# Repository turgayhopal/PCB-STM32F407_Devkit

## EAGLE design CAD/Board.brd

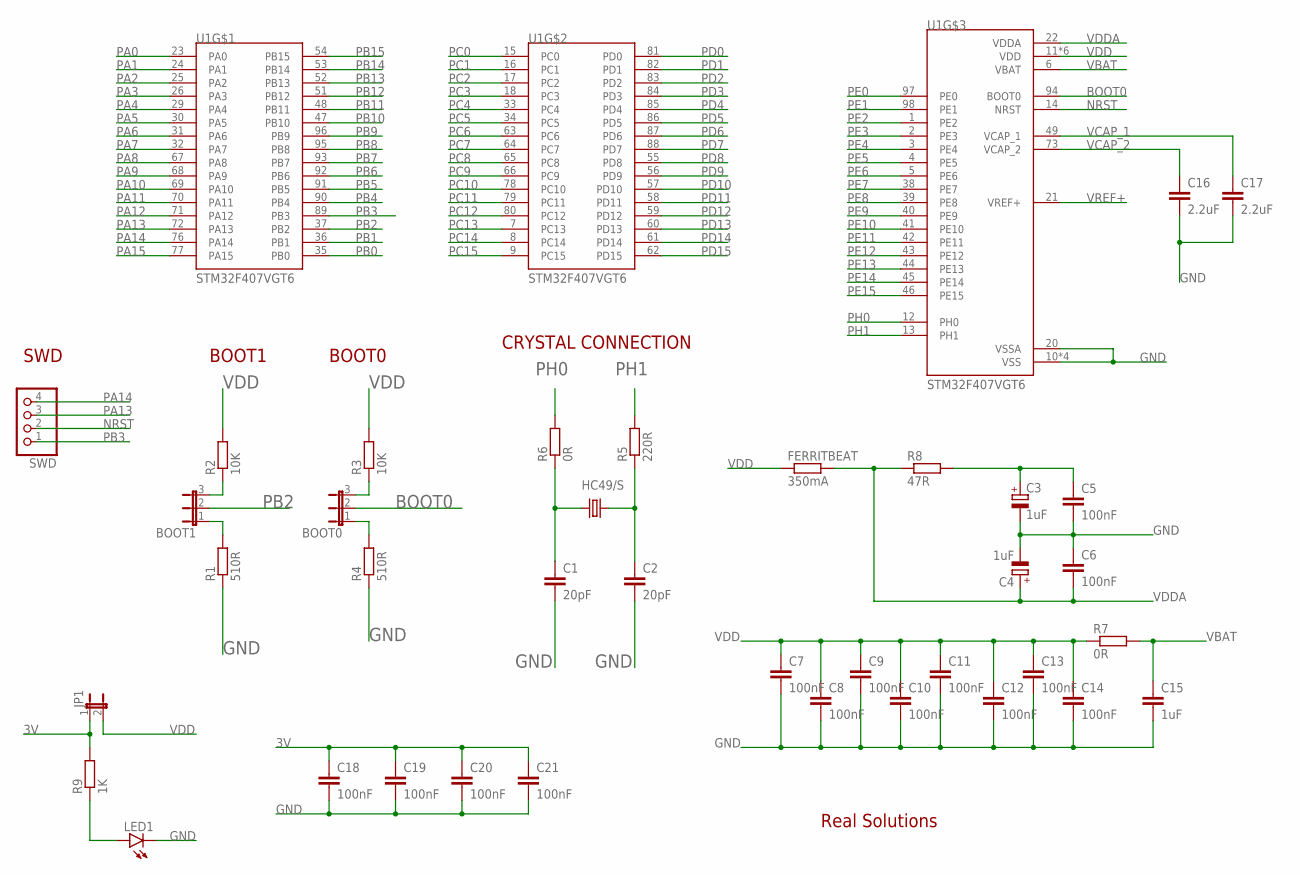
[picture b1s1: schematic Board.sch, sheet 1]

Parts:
BOOT0, BOOT1: JP2E; JP2
C1, C2: 20pF; C0805
C3, C4: 1uF; SMC_A
C5, C6, C7, C8, C9, C10, C11, C12, C13, C14, C18, C19, C20, C21: 100nF; C0805
C15: 1uF; C0805
C16, C17: 2.2uF; C0805
FERRITBEAT: 350mA; R1206
HC49/S: CRYSTALHC49S; HC49/S
JP1: JP1E; JP1
LED1: LEDCHIP-LED0805; CHIP-LED0805
R1, R4: 510R; R0805
R2, R3: 10K; R0805
R5: 220R; R0805
R6, R7: 0R; R0805
R8: 47R; R0805
R9: 1K; R0805
SWD: PINHD-1X4; 1X04
U1: STM32F407VGT6; QFP50P1600X1600X160-100N

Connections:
3V: C18.1, C19.1, C20.1, C21.1, JP1.1, R9.2; also elsewhere on the board
BOOT0: BOOT0.2, U1.94 (BOOT0)
GND: C1.2, C2.2, C3.-, C4.-, C5.2, C6.1, C7.2, C8.2, C9.2, C10.2, C11.2, C12.2, C13.2, C14.2, C15.2, C16.2, C17.2, C18.2, C19.2, C20.2, C21.2, LED1.C, R1.1, R4.1, U1.10 (VSS), U1.20 (VSSA), U1.27 (VSS), U1.74 (VSS), U1.99 (VSS); also elsewhere on the board
unnamed: C1.1, HC49/S.1, R6.1
unnamed: C2.1, HC49/S.2, R5.1
unnamed: BOOT1.3, R2.1
unnamed: BOOT1.1, R1.2
unnamed: BOOT0.3, R3.1
unnamed: BOOT0.1, R4.2
unnamed: LED1.A, R9.1
unnamed: C3.+, C5.1, R8.2
NRST: SWD.2, U1.14 (NRST); also elsewhere on the board
PA0: U1.23 (PA0); also elsewhere on the board
PA1: U1.24 (PA1); also elsewhere on the board
PA2: U1.25 (PA2); also elsewhere on the board
PA3: U1.26 (PA3); also elsewhere on the board
PA4: U1.29 (PA4); also elsewhere on the board
PA5: U1.30 (PA5); also elsewhere on the board
PA6: U1.31 (PA6); also elsewhere on the board
PA7: U1.32 (PA7); also elsewhere on the board
PA8: U1.67 (PA8); also elsewhere on the board
PA9: U1.68 (PA9); also elsewhere on the board
PA10: U1.69 (PA10); also elsewhere on the board
PA11: U1.70 (PA11); also elsewhere on the board
PA12: U1.71 (PA12); also elsewhere on the board
PA13: SWD.3, U1.72 (PA13); also elsewhere on the board
PA14: SWD.4, U1.76 (PA14); also elsewhere on the board
PA15: U1.77 (PA15); also elsewhere on the board
PB0: U1.35 (PB0); also elsewhere on the board
PB1: U1.36 (PB1); also elsewhere on the board
PB2: BOOT1.2, U1.37 (PB2); also elsewhere on the board
PB3: SWD.1, U1.89 (PB3); also elsewhere on the board
PB4: U1.90 (PB4); also elsewhere on the board
PB5: U1.91 (PB5); also elsewhere on the board
PB6: U1.92 (PB6); also elsewhere on the board
PB7: U1.93 (PB7); also elsewhere on the board
PB8: U1.95 (PB8); also elsewhere on the board
PB9: U1.96 (PB9); also elsewhere on the board
PB10: U1.47 (PB10); also elsewhere on the board
PB11: U1.48 (PB11); also elsewhere on the board
PB12: U1.51 (PB12); also elsewhere on the board
PB13: U1.52 (PB13); also elsewhere on the board
PB14: U1.53 (PB14); also elsewhere on the board
PB15: U1.54 (PB15); also elsewhere on the board
PC0: U1.15 (PC0); also elsewhere on the board
PC1: U1.16 (PC1); also elsewhere on the board
PC2: U1.17 (PC2); also elsewhere on the board
PC3: U1.18 (PC3); also elsewhere on the board
PC4: U1.33 (PC4); also elsewhere on the board
PC5: U1.34 (PC5); also elsewhere on the board
PC6: U1.63 (PC6); also elsewhere on the board
PC7: U1.64 (PC7); also elsewhere on the board
PC8: U1.65 (PC8); also elsewhere on the board
PC9: U1.66 (PC9); also elsewhere on the board
PC10: U1.78 (PC10); also elsewhere on the board
PC11: U1.79 (PC11); also elsewhere on the board
PC12: U1.80 (PC12); also elsewhere on the board
PC13: U1.7 (PC13); also elsewhere on the board
PC14: U1.8 (PC14); also elsewhere on the board
PC15: U1.9 (PC15); also elsewhere on the board
PD0: U1.81 (PD0); also elsewhere on the board
PD1: U1.82 (PD1); also elsewhere on the board
PD2: U1.83 (PD2); also elsewhere on the board
PD3: U1.84 (PD3); also elsewhere on the board
PD4: U1.85 (PD4); also elsewhere on the board
PD5: U1.86 (PD5); also elsewhere on the board
PD6: U1.87 (PD6); also elsewhere on the board
PD7: U1.88 (PD7); also elsewhere on the board
PD8: U1.55 (PD8); also elsewhere on the board
PD9: U1.56 (PD9); also elsewhere on the board
PD10: U1.57 (PD10); also elsewhere on the board
PD11: U1.58 (PD11); also elsewhere on the board
PD12: U1.59 (PD12); also elsewhere on the board
PD13: U1.60 (PD13); also elsewhere on the board
PD14: U1.61 (PD14); also elsewhere on the board
PD15: U1.62 (PD15); also elsewhere on the board
PE0: U1.97 (PE0); also elsewhere on the board
PE1: U1.98 (PE1); also elsewhere on the board
PE2: U1.1 (PE2); also elsewhere on the board
PE3: U1.2 (PE3); also elsewhere on the board
PE4: U1.3 (PE4); also elsewhere on the board
PE5: U1.4 (PE5); also elsewhere on the board
PE6: U1.5 (PE6); also elsewhere on the board
PE7: U1.38 (PE7); also elsewhere on the board
PE8: U1.39 (PE8); also elsewhere on the board
PE9: U1.40 (PE9); also elsewhere on the board
PE10: U1.41 (PE10); also elsewhere on the board
PE11: U1.42 (PE11); also elsewhere on the board
PE12: U1.43 (PE12); also elsewhere on the board
PE13: U1.44 (PE13); also elsewhere on the board
PE14: U1.45 (PE14); also elsewhere on the board
PE15: U1.46 (PE15); also elsewhere on the board
PH0: R6.2, U1.12 (PH0)
PH1: R5.2, U1.13 (PH1)
VBAT: C15.1, R7.2, U1.6 (VBAT)
VCAP_1: C17.1, U1.49 (VCAP_1)
VCAP_2: C16.1, U1.73 (VCAP_2)
VDD: C7.1, C8.1, C9.1, C10.1, C11.1, C12.1, C13.1, C14.1, FERRITBEAT.1, JP1.2, R2.2, R3.2, R7.1, U1.11 (VDD), U1.19 (VDD), U1.28 (VDD), U1.50 (VDD), U1.75 (VDD), U1.100 (VDD); also elsewhere on the board
VDDA: C4.+, C6.2, FERRITBEAT.2, R8.1, U1.22 (VDDA)
VREF+: U1.21 (VREF+)

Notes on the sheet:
Real Solutions
SWD
BOOT1
BOOT0
CRYSTAL CONNECTION

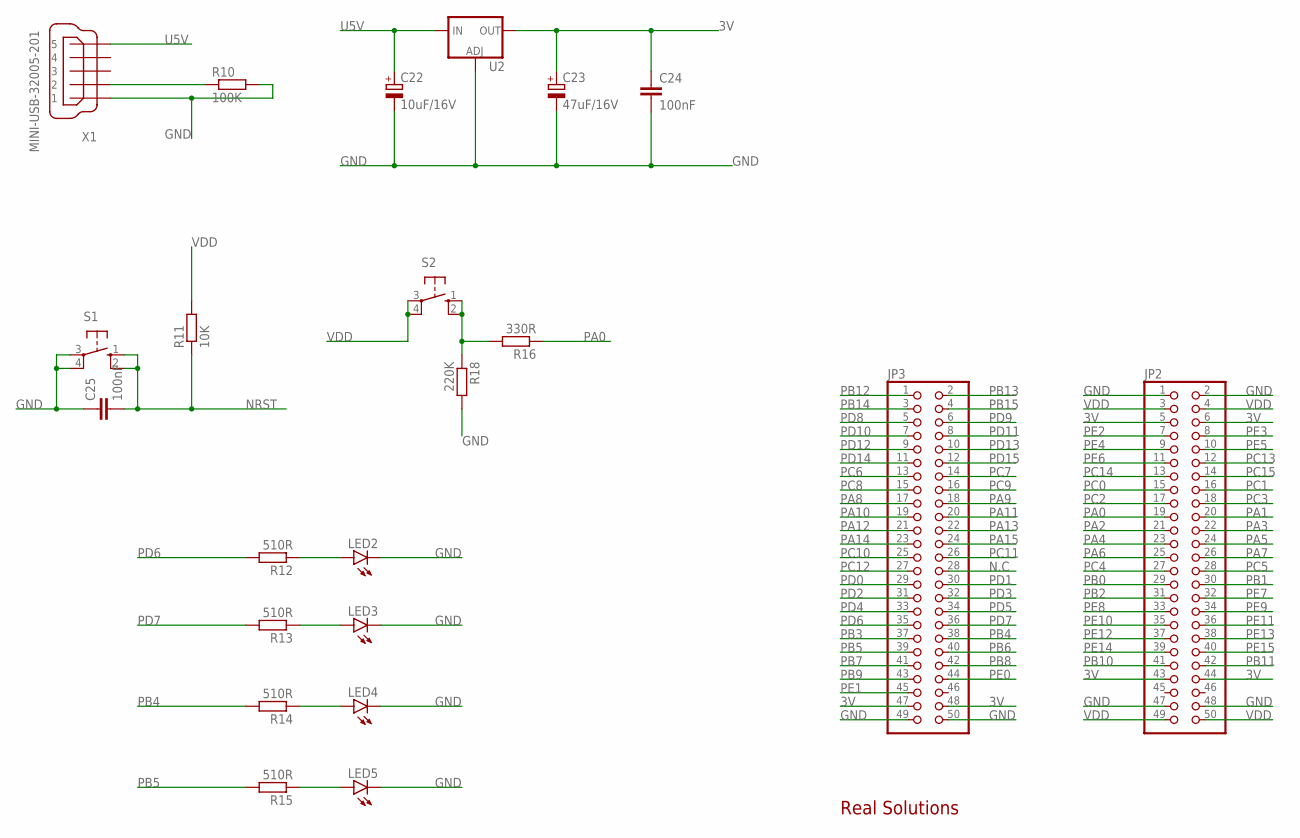
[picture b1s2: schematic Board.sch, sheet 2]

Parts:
C22: 10uF/16V; 153CLV-0405
C23: 47uF/16V; 153CLV-0605
C24, C25: 100nF; C0805
JP2, JP3: PINHD-2X25; 2X25
LED2, LED3, LED4, LED5: LEDCHIP-LED0805; CHIP-LED0805
R10: 100K; R0805
R11: 10K; R0805
R12, R13, R14, R15: 510R; R0805
R16: 330R; R0805
R18: 220K; R0805
S1, S2: 10-XX; B3F-10XX
U2: V_REG_LM1117SOT223; SOT223
X1: MINI-USB-32005-201; 32005-201

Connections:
3V: C23.+, C24.1, JP2.5, JP2.6, JP2.43, JP2.44, JP3.47, JP3.48, U2.2 (OUT), U2.4 (OUT); also elsewhere on the board
GND: C22.-, C23.-, C24.2, C25.1, JP2.1, JP2.2, JP2.47, JP2.48, JP3.49, JP3.50, LED2.C, LED3.C, LED4.C, LED5.C, R10.2, R18.2, S1.3, S1.4 (P1), U2.1 (ADJ), X1.1; also elsewhere on the board
unnamed: LED2.A, R12.1
unnamed: LED3.A, R13.1
unnamed: LED4.A, R14.1
unnamed: R10.1, X1.2
unnamed: LED5.A, R15.1
unnamed: R16.2, R18.1, S2.1 (S), S2.2 (S1)
N.C: JP3.28
NRST: C25.2, R11.1, S1.1 (S), S1.2 (S1); also elsewhere on the board
PA0: JP2.19, R16.1; also elsewhere on the board
PA1: JP2.20; also elsewhere on the board
PA2: JP2.21; also elsewhere on the board
PA3: JP2.22; also elsewhere on the board
PA4: JP2.23; also elsewhere on the board
PA5: JP2.24; also elsewhere on the board
PA6: JP2.25; also elsewhere on the board
PA7: JP2.26; also elsewhere on the board
PA8: JP3.17; also elsewhere on the board
PA9: JP3.18; also elsewhere on the board
PA10: JP3.19; also elsewhere on the board
PA11: JP3.20; also elsewhere on the board
PA12: JP3.21; also elsewhere on the board
PA13: JP3.22; also elsewhere on the board
PA14: JP3.23; also elsewhere on the board
PA15: JP3.24; also elsewhere on the board
PB0: JP2.29; also elsewhere on the board
PB1: JP2.30; also elsewhere on the board
PB2: JP2.31; also elsewhere on the board
PB3: JP3.37; also elsewhere on the board
PB4: JP3.38, R14.2; also elsewhere on the board
PB5: JP3.39, R15.2; also elsewhere on the board
PB6: JP3.40; also elsewhere on the board
PB7: JP3.41; also elsewhere on the board
PB8: JP3.42; also elsewhere on the board
PB9: JP3.43; also elsewhere on the board
PB10: JP2.41; also elsewhere on the board
PB11: JP2.42; also elsewhere on the board
PB12: JP3.1; also elsewhere on the board
PB13: JP3.2; also elsewhere on the board
PB14: JP3.3; also elsewhere on the board
PB15: JP3.4; also elsewhere on the board
PC0: JP2.15; also elsewhere on the board
PC1: JP2.16; also elsewhere on the board
PC2: JP2.17; also elsewhere on the board
PC3: JP2.18; also elsewhere on the board
PC4: JP2.27; also elsewhere on the board
PC5: JP2.28; also elsewhere on the board
PC6: JP3.13; also elsewhere on the board
PC7: JP3.14; also elsewhere on the board
PC8: JP3.15; also elsewhere on the board
PC9: JP3.16; also elsewhere on the board
PC10: JP3.25; also elsewhere on the board
PC11: JP3.26; also elsewhere on the board
PC12: JP3.27; also elsewhere on the board
PC13: JP2.12; also elsewhere on the board
PC14: JP2.13; also elsewhere on the board
PC15: JP2.14; also elsewhere on the board
PD0: JP3.29; also elsewhere on the board
PD1: JP3.30; also elsewhere on the board
PD2: JP3.31; also elsewhere on the board
PD3: JP3.32; also elsewhere on the board
PD4: JP3.33; also elsewhere on the board
PD5: JP3.34; also elsewhere on the board
PD6: JP3.35, R12.2; also elsewhere on the board
PD7: JP3.36, R13.2; also elsewhere on the board
PD8: JP3.5; also elsewhere on the board
PD9: JP3.6; also elsewhere on the board
PD10: JP3.7; also elsewhere on the board
PD11: JP3.8; also elsewhere on the board
PD12: JP3.9; also elsewhere on the board
PD13: JP3.10; also elsewhere on the board
PD14: JP3.11; also elsewhere on the board
PD15: JP3.12; also elsewhere on the board
PE0: JP3.44; also elsewhere on the board
PE1: JP3.45; also elsewhere on the board
PE2: JP2.7; also elsewhere on the board
PE3: JP2.8; also elsewhere on the board
PE4: JP2.9; also elsewhere on the board
PE5: JP2.10; also elsewhere on the board
PE6: JP2.11; also elsewhere on the board
PE7: JP2.32; also elsewhere on the board
PE8: JP2.33; also elsewhere on the board
PE9: JP2.34; also elsewhere on the board
PE10: JP2.35; also elsewhere on the board
PE11: JP2.36; also elsewhere on the board
PE12: JP2.37; also elsewhere on the board
PE13: JP2.38; also elsewhere on the board
PE14: JP2.39; also elsewhere on the board
PE15: JP2.40; also elsewhere on the board
U5V: C22.+, U2.3 (IN), X1.5
VDD: JP2.3, JP2.4, JP2.49, JP2.50, R11.2, S2.3, S2.4 (P1); also elsewhere on the board

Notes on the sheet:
Real Solutions

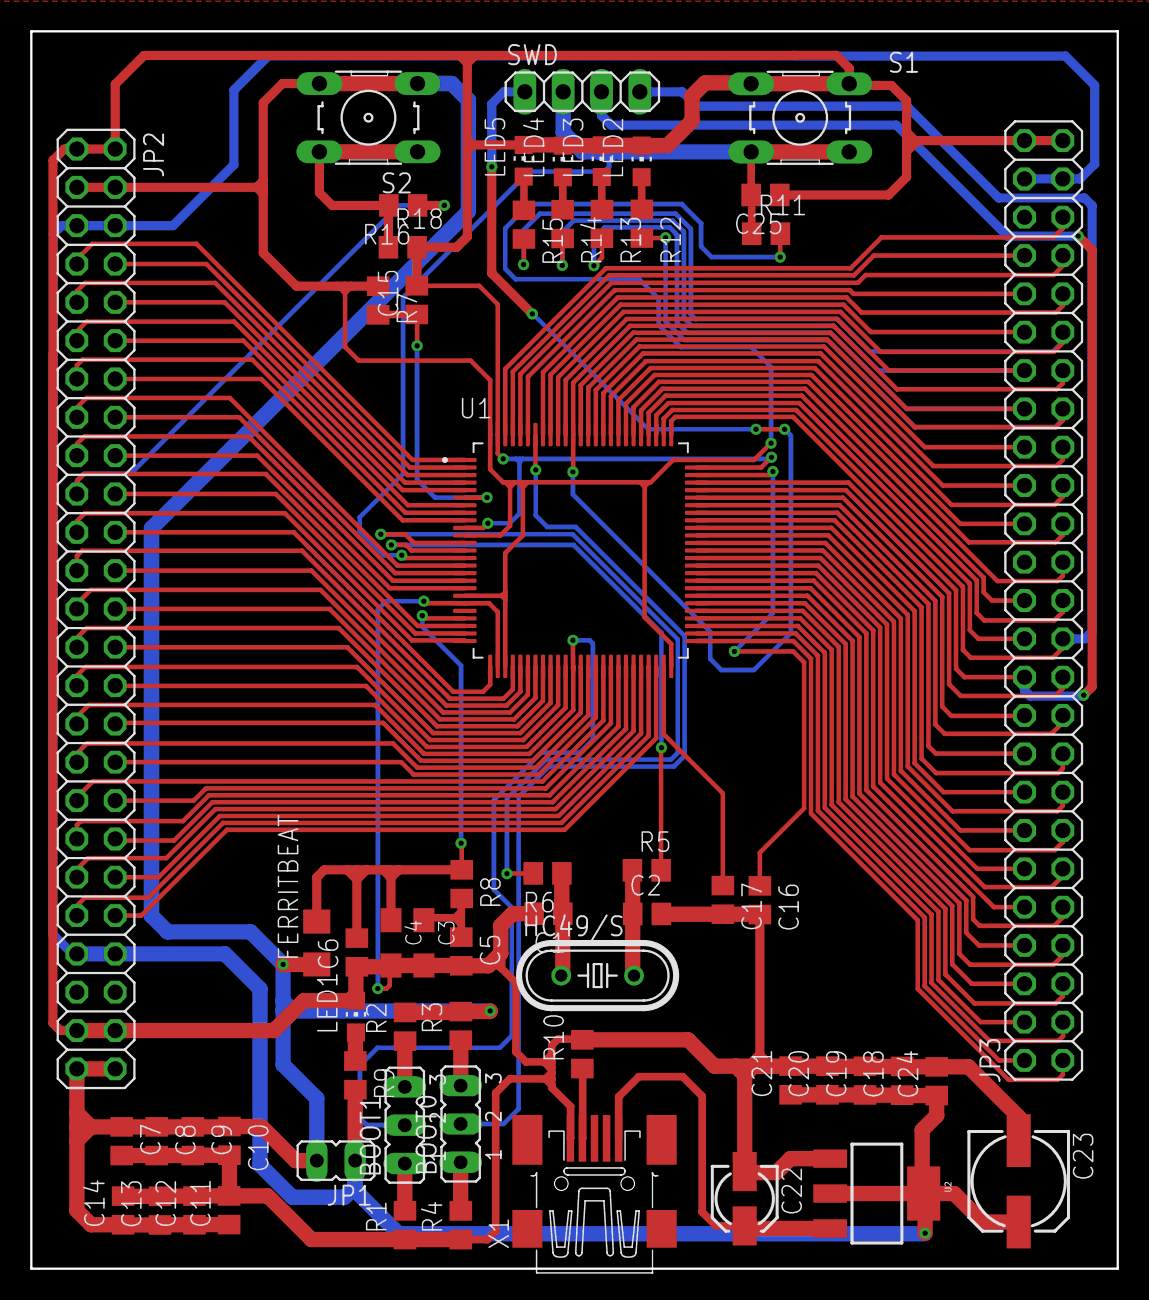
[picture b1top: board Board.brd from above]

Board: 2 copper layers, 72.0 x 82.0 mm, 60 parts (0 on the bottom side), 106 nets.

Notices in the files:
parts and their libraries:
SparkFun-IC-Power: Licensing: Creative Commons ShareAlike 4.0 International - https://creativecommons.org/licenses/by-sa/4.0
